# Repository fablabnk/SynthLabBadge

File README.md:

A light-to-sound badge-synth based on Dylan B's open-hardware Beam Catcher project and coming out of our weekly SynthLab audio hardware meetups at fablab|nk. The badge is designed to be a first-intro to DIY synthesiser building for new visitors. 

Check the [PDF build guide](./BuildGuide/SynthLabBadgeBuildGuide.pdf).

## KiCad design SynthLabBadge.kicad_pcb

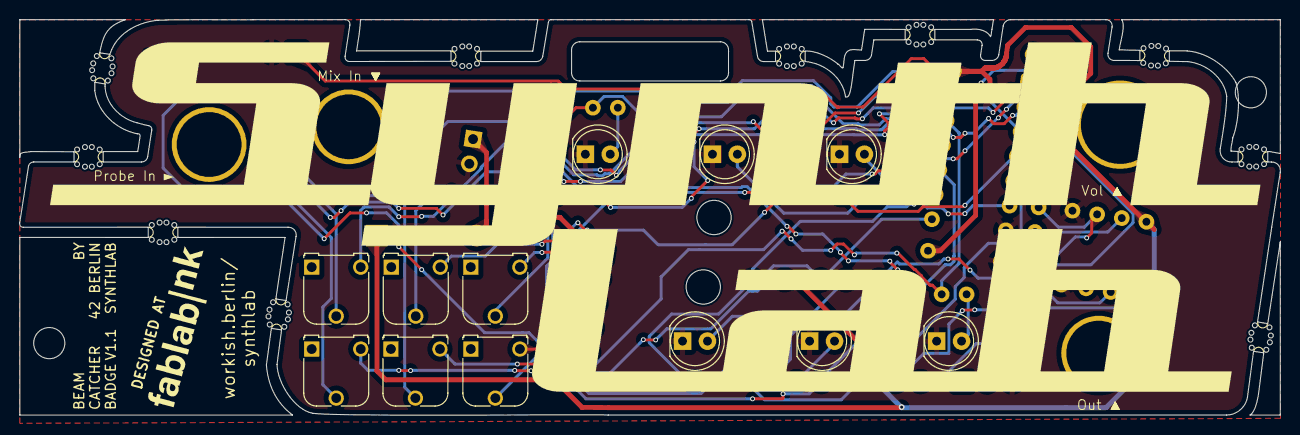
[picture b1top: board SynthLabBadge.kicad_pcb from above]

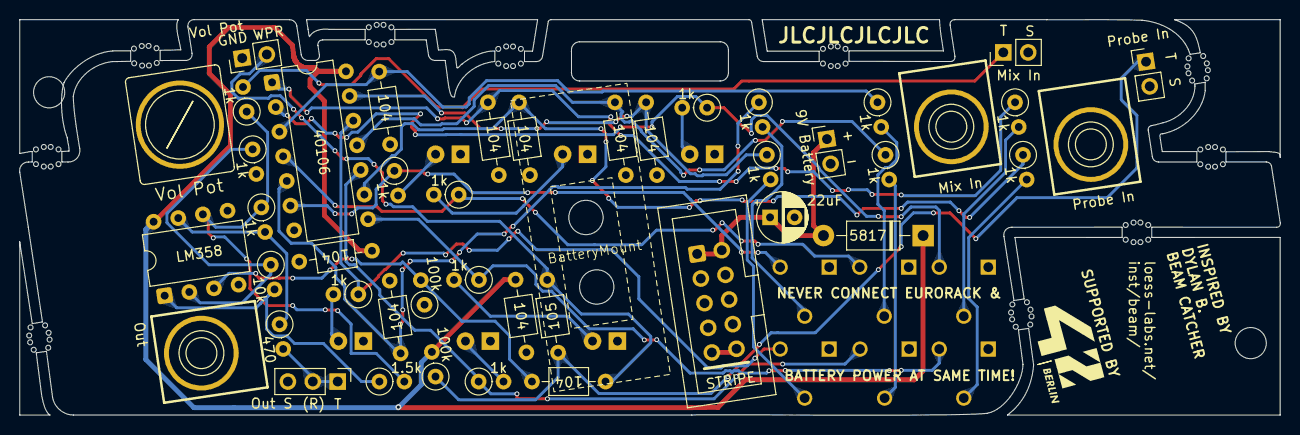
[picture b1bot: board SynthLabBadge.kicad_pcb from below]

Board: 2 copper layers, 128.5 x 40.3 mm, 71 parts (45 on the bottom side), 37 nets.

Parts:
BT1: 9V Battery; PinHeader_1x02_P2.54mm_Vertical
BatteryMount: 9VBatteryClop
C1: 1uF; C_Axial_L3.8mm_D2.6mm_P7.50mm_Horizontal_Disc3DModel
C2, C3, C4, C5, C6, C7, C8, C9, C10: 100nF; C_Axial_L3.8mm_D2.6mm_P7.50mm_Horizontal_Disc3DModel
C11: 22uF; CP_Radial_D5.0mm_P2.50mm
D2, D3, D4, D5, D6, D7: LED; LED_D5.0mm_Lowered
D8: 5817; D_DO-41_SOD81_P10.16mm_Horizontal
J2: Probe In; Faceplate_Hole_Jack_3.5mm_NoPadNumber
J2#2: Probe In; EighthInch_PJ398SM_Silkscreen_Courtyard_Only
J3: Mix_In; Faceplate_Hole_Jack_3.5mm_NoPadNumber
J3#2: Mix In; EighthInch_PJ398SM_Silkscreen_Courtyard_Only
J4: Out; Faceplate_Hole_Jack_3.5mm_NoPadNumber
J4#2: Out; EighthInch_PJ398SM_Silkscreen_Courtyard_Only
J5: Eurorack_Power_10pin_Unshrouded; IDC-Header_2x05_P2.54mm_Vertical_Euro_Power_Striped_Thicker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
J6: Mix In; PinHeader_1x02_P2.54mm_Vertical
J7: Probe In; PinHeader_1x02_P2.54mm_Vertical
J8: Out; PinHeader_1x03_P2.54mm_Vertical
J9: Vol Pot; PinHeader_1x02_P2.54mm_Vertical
R1, R2, R5, R7, R8, R9, R10, R12, R13, R14, R15, R16, R17, R18, R19: 1k; R_Axial_DIN0207_L6.3mm_D2.5mm_P2.54mm_Vertical
R3, R20: 100k; R_Axial_DIN0207_L6.3mm_D2.5mm_P2.54mm_Vertical
R4: 10k; R_Axial_DIN0207_L6.3mm_D2.5mm_P2.54mm_Vertical
R6: 1.5k; R_Axial_DIN0207_L6.3mm_D2.5mm_P2.54mm_Vertical
R11: 470; R_Axial_DIN0207_L6.3mm_D2.5mm_P2.54mm_Vertical
RV1, RV2, RV4, RV5, RV6, RV7: 1M; Potentiometer_Runtron_RM-065_Vertical_With3DModel
RV3: 100K; Faceplate_Hole_Jack_3.5mm_NoPadNumber
RV3#2: 100K; Pot_9mm_DShaft_Silkscreen_Courtyard_Only
U1: LM358; DIP-8_W7.62mm
U2: CD40106BPWR; DIP-14_W7.62mm
mouse-bite-1mm-slot, mouse-bite-1mm-slot#2, mouse-bite-1mm-slot#3, mouse-bite-1mm-slot#4, mouse-bite-1mm-slot#5, mouse-bite-1mm-slot#6, mouse-bite-1mm-slot#7, mouse-bite-1mm-slot#8, mouse-bite-1mm-slot#9, mouse-bite-1mm-slot#10: VAL**; mouse-bite-1mm-slot

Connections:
GND: BT1.2 (-), C3.2, C4.2, C5.2, C6.2, C7.2, C8.2, C9.2, C10.2, C11.2, D2.1 (K), D3.1 (K), D4.1 (K), D5.1 (K), D6.1 (K), D7.1 (K), J5.3 (GND), J5.4 (GND), J5.5 (GND), J5.6 (GND), J5.7 (GND), J5.8 (GND), J6.S (Pin_2), J7.S (Pin_2), J8.S (Pin_3), J9.1, R3.1, R5.2, U1.4 (V-), U1.5 (+), U2.7 (VSS)
unnamed: BT1.1 (+), C11.1, D8.2 (A), J5.1 (+12V), J5.2 (+12V)
unnamed: D2.2 (A), R14.2
unnamed: D3.2 (A), R17.2
unnamed: D4.2 (A), R15.2
unnamed: D5.2 (A), R18.2
unnamed: D6.2 (A), R16.2
unnamed: D7.2 (A), R19.2
unnamed: J5.9 (-12V), J5.10 (-12V)
unnamed: J6.T (Pin_1), R10.2
unnamed: C1.1, J7.T (Pin_1), R20.1
unnamed: J8.R (Pin_1), J8.T (Pin_2), R11.2
unnamed: C1.2, C2.1, J9.2
unnamed: R1.2, RV1.2
unnamed: R2.2, RV2.2
unnamed: R4.2, R6.1, U1.1
unnamed: R8.2, RV4.2
unnamed: R9.2, RV5.2
unnamed: R7.2, R11.1, U1.7
unnamed: R12.2, RV6.2
unnamed: R13.2, RV7.2
unnamed: C2.2, R3.2, U1.3 (+)
unnamed: R4.1, R5.1, U1.2 (-)
unnamed: R6.2, R7.1, R10.1, U1.6 (-)
unnamed: C4.1, R1.1, U2.1 (I)
unnamed: R14.1, RV1.3, U2.2 (O)
unnamed: C5.1, R2.1, U2.3 (I)
unnamed: R17.1, RV2.3, U2.4 (O)
unnamed: C6.1, R8.1, U2.5 (I)
unnamed: R15.1, RV4.3, U2.6 (O)
unnamed: C7.1, R9.1, U2.9 (I)
unnamed: R18.1, RV5.3, U2.8 (O)
unnamed: C8.1, R12.1, U2.11 (I)
unnamed: R16.1, RV6.3, U2.10 (O)
unnamed: C9.1, R13.1, U2.13 (I)
unnamed: R19.1, RV7.3, U2.12 (O)
VCC: C3.1, C10.1, D8.1 (K), R20.2, U1.8 (V+), U2.14 (VDD)

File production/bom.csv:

Designator,Footprint,Quantity,Value,LCSC Part #
,,1,,
BT1,PinHeader_1x02_P2.54mm_Vertical,1,9V Bat,
C1,C_Axial_L3.8mm_D2.6mm_P7.50mm_Horizontal,1,1uF,
"C10, C2, C3, C4, C5, C6, C7, C8, C9",C_Axial_L3.8mm_D2.6mm_P7.50mm_Horizontal,9,100nF,
C11,CP_Radial_D5.0mm_P2.50mm,1,22uF,
"D2, D3, D4, D5, D6, D7",LED_D5.0mm,6,LED,
D8,D_DO-41_SOD81_P10.16mm_Horizontal,1,5817,
J2_2,Faceplate_Hole_Jack_3.5mm_NoPadNumber,1,Probe In,
J2,EighthInch_PJ398SM_Silkscreen_Courtyard_Only,1,Probe In,
J3_2,Faceplate_Hole_Jack_3.5mm_NoPadNumber,1,Mix_In,
J3,EighthInch_PJ398SM_Silkscreen_Courtyard_Only,1,Mix_In,
J4_2,Faceplate_Hole_Jack_3.5mm_NoPadNumber,1,Out,
J4,EighthInch_PJ398SM_Silkscreen_Courtyard_Only,1,Out,
J5,IDC-Header_2x05_P2.54mm_Vertical_Euro_Power_Striped_ThickerText,1,Eurorack_Power_10pin_Unshrouded,
J6,PinHeader_1x02_P2.54mm_Vertical,1,Mix In,
J7,PinHeader_1x02_P2.54mm_Vertical,1,Probe,
J8,PinHeader_1x03_P2.54mm_Vertical,1,Conn_Out,
J9,PinHeader_1x02_P2.54mm_Vertical,1,Vol Pot,
JP1,SolderJumper-2_P1.3mm_Open_RoundedPad1.0x1.5mm,1,Jmp4Stereo,
"MOUSE-BITE-1MM-SLOT_10, MOUSE-BITE-1MM-SLOT_9, MOUSE-BITE-1MM-SLOT_8, MOUSE-BITE-1MM-SLOT_7, MOUSE-BITE-1MM-SLOT_6, MOUSE-BITE-1MM-SLOT_5, MOUSE-BITE-1MM-SLOT_4, MOUSE-BITE-1MM-SLOT_3, MOUSE-BITE-1MM-SLOT_2, MOUSE-BITE-1MM-SLOT",mouse-bite-1mm-slot,10,VAL**,
"R1, R10, R12, R13, R2, R5, R6, R7, R8, R9",R_Axial_DIN0207_L6.3mm_D2.5mm_P10.16mm_Horizontal,10,1k,
R11,R_Axial_DIN0207_L6.3mm_D2.5mm_P10.16mm_Horizontal,1,470,
"R14, R15, R16, R17, R18, R19, R3",R_Axial_DIN0207_L6.3mm_D2.5mm_P10.16mm_Horizontal,7,100k,
R4,R_Axial_DIN0207_L6.3mm_D2.5mm_P10.16mm_Horizontal,1,500k1M,
"RV1, RV2, RV4, RV5, RV6, RV7",Potentiometer_Runtron_RM-065_Vertical,6,1M,
RV3_2,Faceplate_Hole_Jack_3.5mm_NoPadNumber,1,100K,
RV3,Pot_9mm_DShaft_Silkscreen_Courtyard_Only,1,100K,
U1,DIP-8_W7.62mm,1,LM358,
U2,DIP-14_W7.62mm,1,CD40106BPWR,

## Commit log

2025-07-24 finalising silkscreening
2025-07-24 final check before production
2025-07-24 committing before sending to production
2025-11-29 commiting before trying to move components from bottom of board
2025-11-30 V1.1 ready for production
2025-11-30 V1.1 ready for production - barring lanyard hole check
2025-12-20 All 3D models added and positioned - ready to create build guide
2025-12-20 increased height of battery clip
2025-12-20 Pushing before propagating mono jack screws to other footprints
2025-12-20 Footprints updated - screws and nuts now added to 3D models
2025-12-20 added battery clip and build guide screenshots
2025-12-21 Committing before creating temp broken-out version of board for build guide
2025-12-26 Added build guide for 39C3 workshop
